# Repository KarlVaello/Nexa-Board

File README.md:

### NOTES!

In need of satisfying the ISO 15765-2 the board will receive hardware changes.

ISO 15765-2, or ISO-TP (Transport Layer), is an international standard for sending data packets over a CAN-Bus. The protocol allows for the transport of messages that exceed the eight byte maximum payload of CAN frames. ISO-TP segments longer messages into multiple frames, adding metadata that allows the interpretation of individual frames and reassembly into a complete message packet by the recipient. It can carry up to 4095 bytes of payload per message packet.

Full duplex RS-485 will be replaced by CAN-bus.

### What is Nexa-Board?
Nexa-Board is an open source project, based on STM32F103 microcontroller with a full duplex RS-485 to create a multipoint network that allows receiving and sending the information of all the boards.
RS-485 as a physical layer and by programming you can set your own data exchange and interpretation protocol.

Hardware characteristics
-	72 MHz
-	Full duplex RS-485 fully configurable.
- CAN-BUS
-	17 GPIO pins
- 7 to 15 V power input
-	Power input polarity protection

### Why does it exist ?
Exist as a solution to get a fully configurable comunication protocol, that allow you to create your own protocol depending on your needs.

### Getting Started
- Get a Nexa Board

### Project that use Nexa-Board
- Nexa Home

### TODO 
- [x] Board design (Schematic)
- [x] Board design (PCB)
- [x] PCB manufacture
- [ ] HW test
- [ ] HW final version
---------------
- [ ] New hardware changes due to apply CAN-bus
- [x] Board design (Schematic)
- [x] Board design (PCB)
- [x] PCB manufacture
- [ ] HW test
- [ ] HW final version

### Releases
 | [v1.0](https://github.com/KarlVaello/Nexa-Board/releases/tag/v1.0) - Initial complete board concept

### License
- [GPL-3.0](https://github.com/KarlVaello/Nexa-Board/blob/master/LICENSE.md)

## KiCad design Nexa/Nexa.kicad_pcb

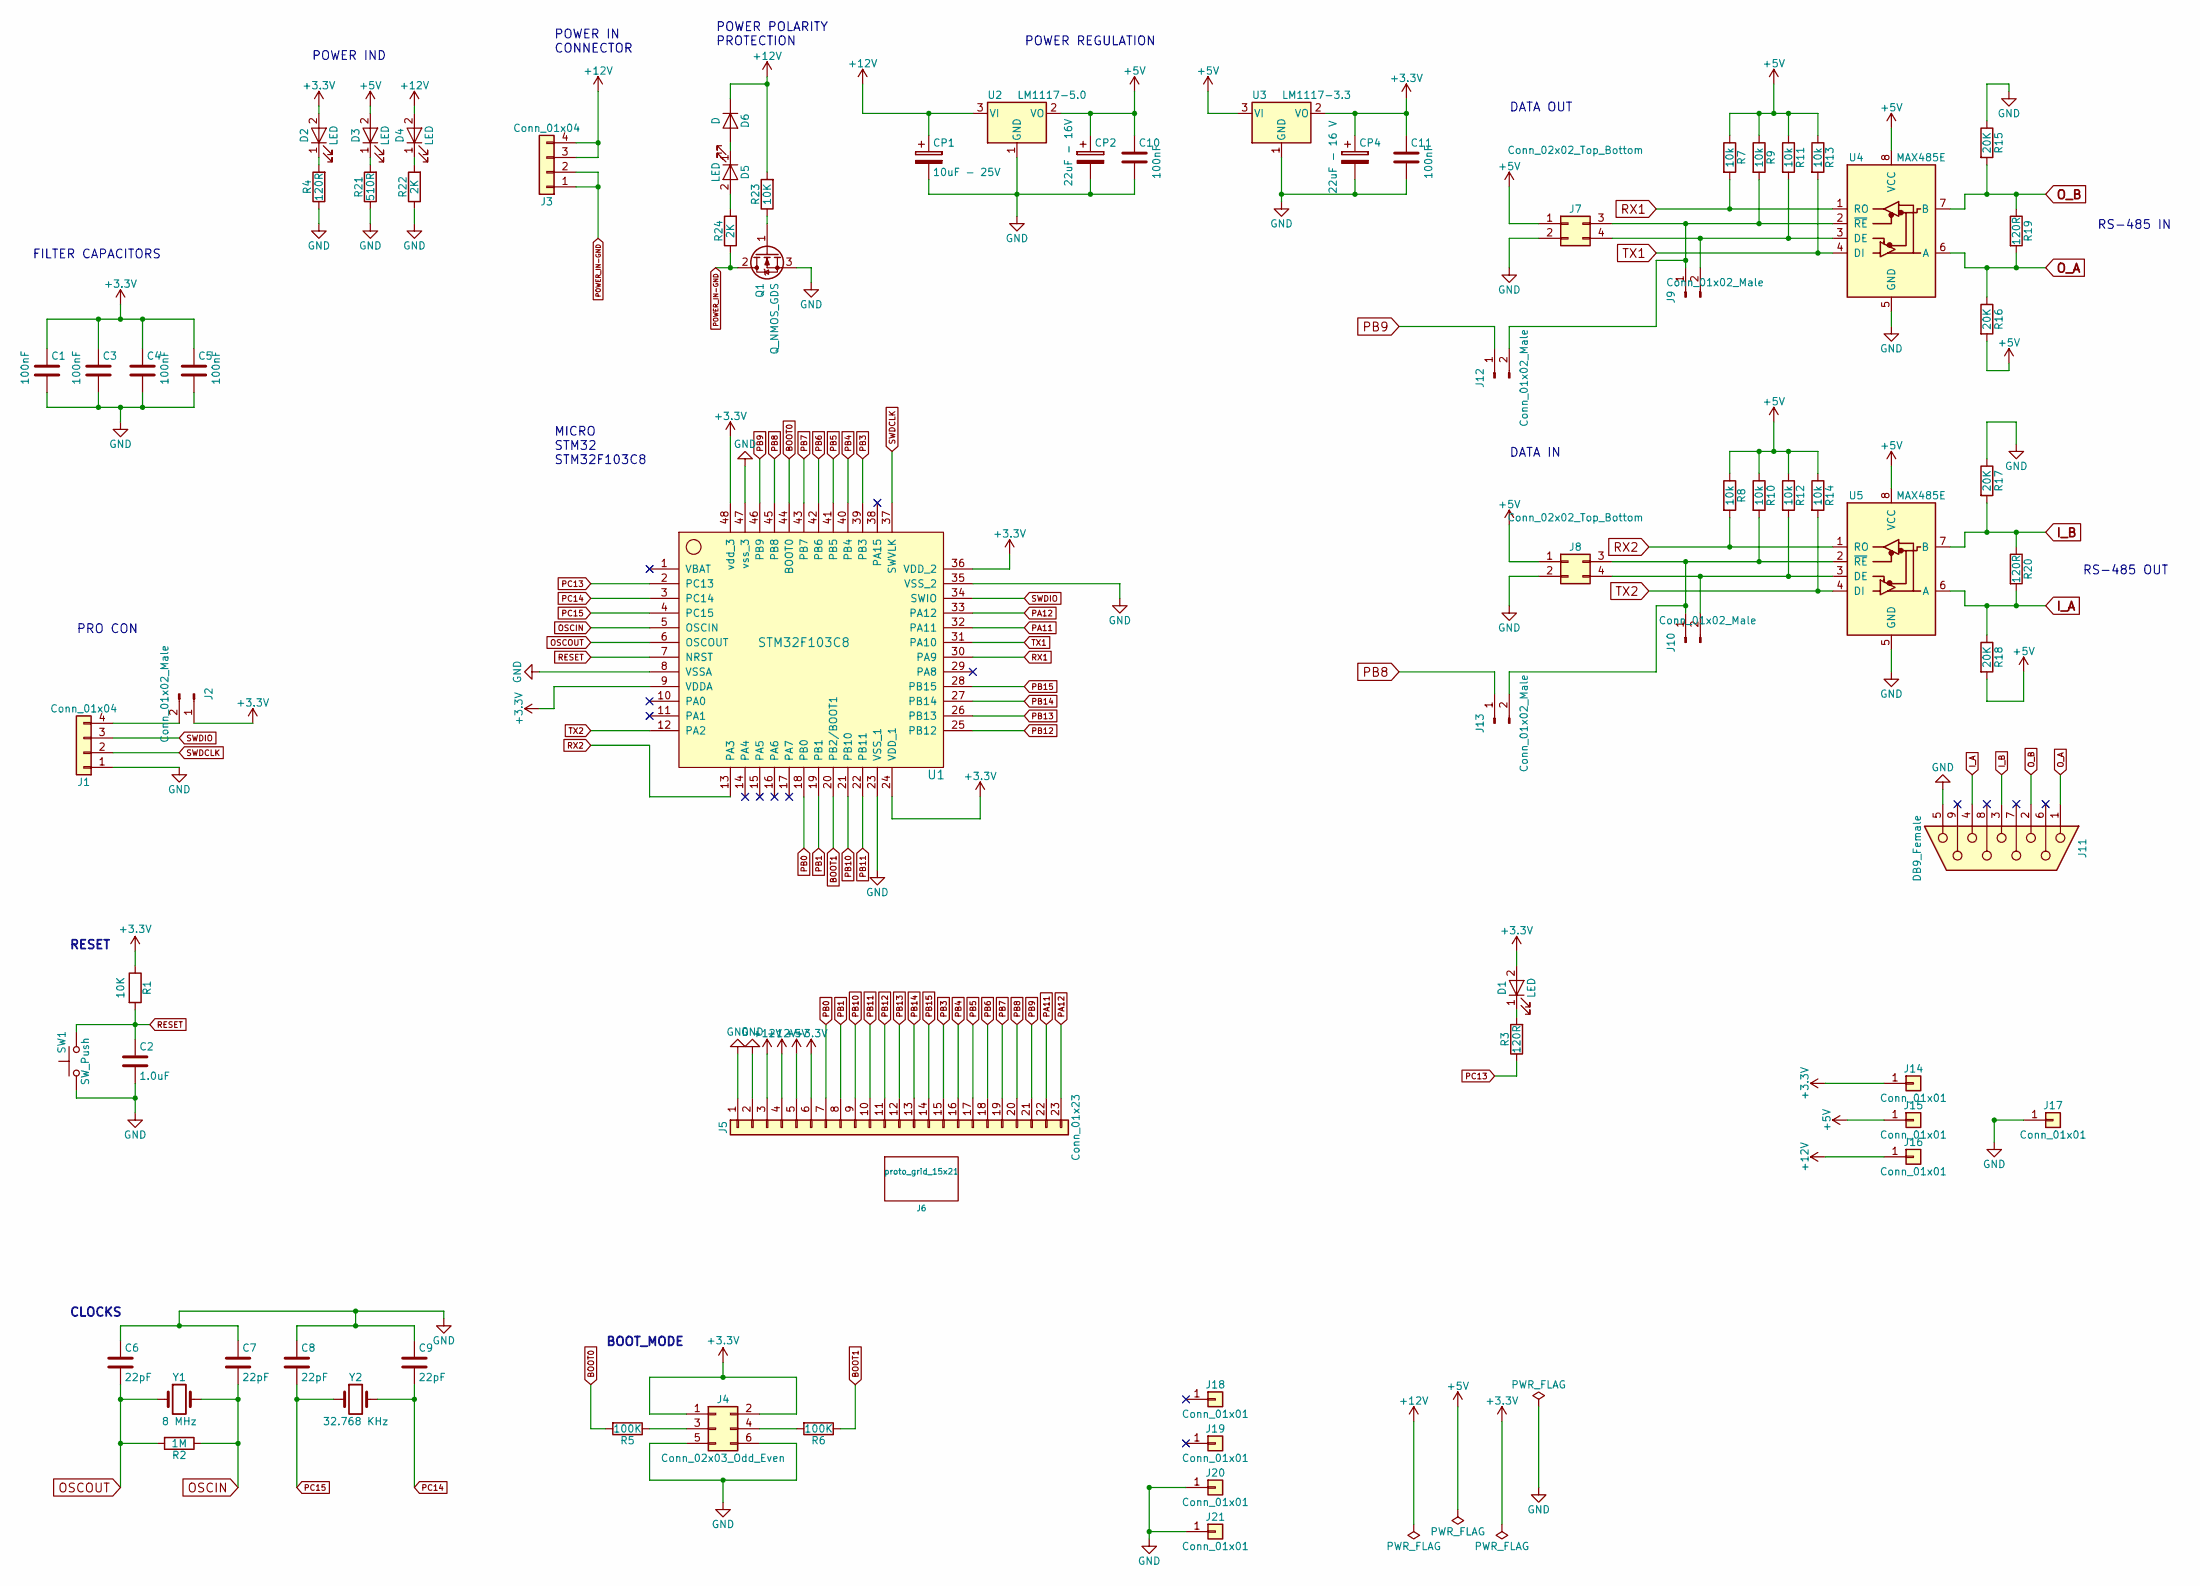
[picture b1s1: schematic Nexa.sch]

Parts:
C1, C3, C4, C5: 100nF; C_0603_HandSoldering
C2: 1.0uF; C_0603_HandSoldering
C6, C7, C8, C9: 22pF; C_0603_HandSoldering
C10, C11: 100nF; C_0805_HandSoldering
CP1: 10uF - 25V; CP_Tantalum_Case-C_EIA-6032-28_Hand
CP2: 22uF - 16V; CP_Tantalum_Case-B_EIA-3528-21_Hand
CP4: 22uF - 16 V; CP_Tantalum_Case-B_EIA-3528-21_Hand
D1, D2, D3, D4, D5: LED; LED_0805_HandSoldering
D6: D; D_SMB
J1: Conn_01x04; Pin_Header_Straight_1x04_Pitch2.54mm
J2, J9, J10, J12, J13: Conn_01x02_Male; Pin_Header_Straight_1x02_Pitch2.54mm
J3: Conn_01x04; Molex_MiniFit-JR-5569-04A2_2x02x4.20mm_Angled
J4: Conn_02x03_Odd_Even; Pin_Header_Straight_2x03_Pitch2.54mm
J5: Conn_01x23; Socket_Strip_Straight_1x23_Pitch2.54mm
J6: proto_grid_15x21; grid
J7, J8: Conn_02x02_Top_Bottom; Pin_Header_Straight_2x02_Pitch2.54mm
J11: DB9_Female
J14, J15, J16: Conn_01x01; Pin_Header_Straight_1x01_Pitch2.54mm
J17: Conn_01x01; Measurement_Point_Round-TH_Small
J18, J19, J20, J21: Conn_01x01; MountHoles_H3.2mm_D5.5
Q1: Q_NMOS_GDS; TO-252-2
R1, R23: 10K; R_0603_HandSoldering
R2: 1M; R_0603_HandSoldering
R3, R4, R19, R20: 120R; R_0603_HandSoldering
R5, R6: 100K; R_0603_HandSoldering
R7, R8, R9, R10, R11, R12, R13, R14: 10k; R_0603_HandSoldering
R15, R16, R17, R18: 20K; R_0603_HandSoldering
R21: 510R; R_0603_HandSoldering
R22, R24: 2K; R_0603_HandSoldering
SW1: SW_Push; SW_PUSH_6mm_h8.5mm
U1: STM32F103C8; LQFP-48_7x7mm_Pitch0.5mm
U2: LM1117-5.0; SOT-223
U3: LM1117-3.3; SOT-223
U4, U5: MAX485E; SOIC-8_3.9x4.9mm_Pitch1.27mm
Y1: 8 MHz; Crystal_HC49-4H_Vertical
Y2: 32.768 KHz; Crystal_SMD_SeikoEpson_MC306-4pin_8.0x3.2mm_HandSoldering

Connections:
+3V3: C1.1, C3.1, C4.1, C5.1, C11.1, CP4.1, D1.2 (A), D2.2 (A), J2.1, J4.1, J4.2, J5.6, J14.1, R1.1, U1.9 (VDDA), U1.24 (VDD_1), U1.36 (VDD_2), U1.48 (vdd_3), U3.2 (VO)
+5V: C10.1, CP2.1, D3.2 (A), J5.5, J7.1, J8.1, J15.1, R7.1, R8.1, R9.1, R10.1, R11.1, R12.1, R13.1, R14.1, R16.2, R18.2, U2.2 (VO), U3.3 (VI), U4.8 (VCC), U5.8 (VCC)
+12V: CP1.1, D4.2 (A), D6.1 (K), J3.3, J3.4, J5.3, J5.4, J16.1, R23.2, U2.3 (VI)
BOOT0: R5.2, U1.44 (BOOT0)
BOOT1: R6.1, U1.20 (PB2/BOOT1)
GND: C1.2, C2.2, C3.2, C4.2, C5.2, C6.1, C7.1, C8.1, C9.1, C10.2, C11.2, CP1.2, CP2.2, CP4.2, J1.1, J4.5, J4.6, J5.1, J5.2, J7.2, J8.2, J11.5, J17.1, J20.1, J21.1, Q1.3 (S), R4.1, R15.1, R17.1, R21.1, R22.1, SW1.1, U1.8 (VSSA), U1.23 (VSS_1), U1.35 (VSS_2), U1.47 (vss_3), U2.1 (GND), U3.1 (GND), U4.5 (GND), U5.5 (GND)
I_A: J11.4, R18.1, R20.2, U5.6 (A)
I_B: J11.3, R17.2, R20.1, U5.7 (B)
unnamed: D1.1 (K), R3.2
unnamed: D2.1 (K), R4.2
unnamed: D3.1 (K), R21.2
unnamed: D4.1 (K), R22.2
unnamed: D5.1 (K), D6.2 (A)
unnamed: D5.2 (A), R24.2
unnamed: J1.4, J2.2
unnamed: J4.3, R5.1
unnamed: J4.4, R6.2
unnamed: J7.4, J9.2, R11.2, U4.3 (DE)
unnamed: J8.3, J10.1, J13.2, R10.2, U5.2 (~RE)
unnamed: J8.4, J10.2, R12.2, U5.3 (DE)
unnamed: J7.3, J9.1, J12.2, R9.2, U4.2 (~RE)
unnamed: Q1.1 (G), R23.1
OSCIN: C7.2, R2.1, U1.5 (OSCIN), Y1.2
OSCOUT: C6.2, R2.2, U1.6 (OSCOUT), Y1.1
O_A: J11.1, R16.1, R19.2, U4.6 (A)
O_B: J11.2, R15.2, R19.1, U4.7 (B)
PA11: J5.22, U1.32 (PA11)
PA12: J5.23, U1.33 (PA12)
PB0: J5.7, U1.18 (PB0)
PB1: J5.8, U1.19 (PB1)
PB3: J5.15, U1.39 (PB3)
PB4: J5.16, U1.40 (PB4)
PB5: J5.17, U1.41 (PB5)
PB6: J5.18, U1.42 (PB6)
PB7: J5.19, U1.43 (PB7)
PB8: J5.20, J13.1, U1.45 (PB8~)
PB9: J5.21, J12.1, U1.46 (PB9)
PB10: J5.9, U1.21 (PB10)
PB11: J5.10, U1.22 (PB11)
PB12: J5.11, U1.25 (PB12)
PB13: J5.12, U1.26 (PB13)
PB14: J5.13, U1.27 (PB14)
PB15: J5.14, U1.28 (PB15)
PC13: R3.1, U1.2 (PC13)
PC14: C9.2, U1.3 (PC14), Y2.2
PC15: C8.2, U1.4 (PC15), Y2.1
POWER_IN-GND: J3.1, J3.2, Q1.2 (D), R24.1
RESET: C2.1, R1.2, SW1.2, U1.7 (NRST)
RX1: R7.2, U1.30 (PA9), U4.1 (RO)
RX2: R8.2, U1.13 (PA3), U5.1 (RO)
SWDCLK: J1.2, U1.37 (SWVLK)
SWDIO: J1.3, U1.34 (SWIO)
TX1: R13.2, U1.31 (PA10), U4.4 (DI)
TX2: R14.2, U1.12 (PA2), U5.4 (DI)

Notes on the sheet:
DATA OUT
DATA IN
RESET
CLOCKS
BOOT_MODE
FILTER CAPACITORS
POWER REGULATION
RS-485 IN
RS-485 OUT
POWER IND
POWER POLARITY PROTECTION
POWER IN CONNECTOR
PRO CON
MICRO STM32 STM32F103C8

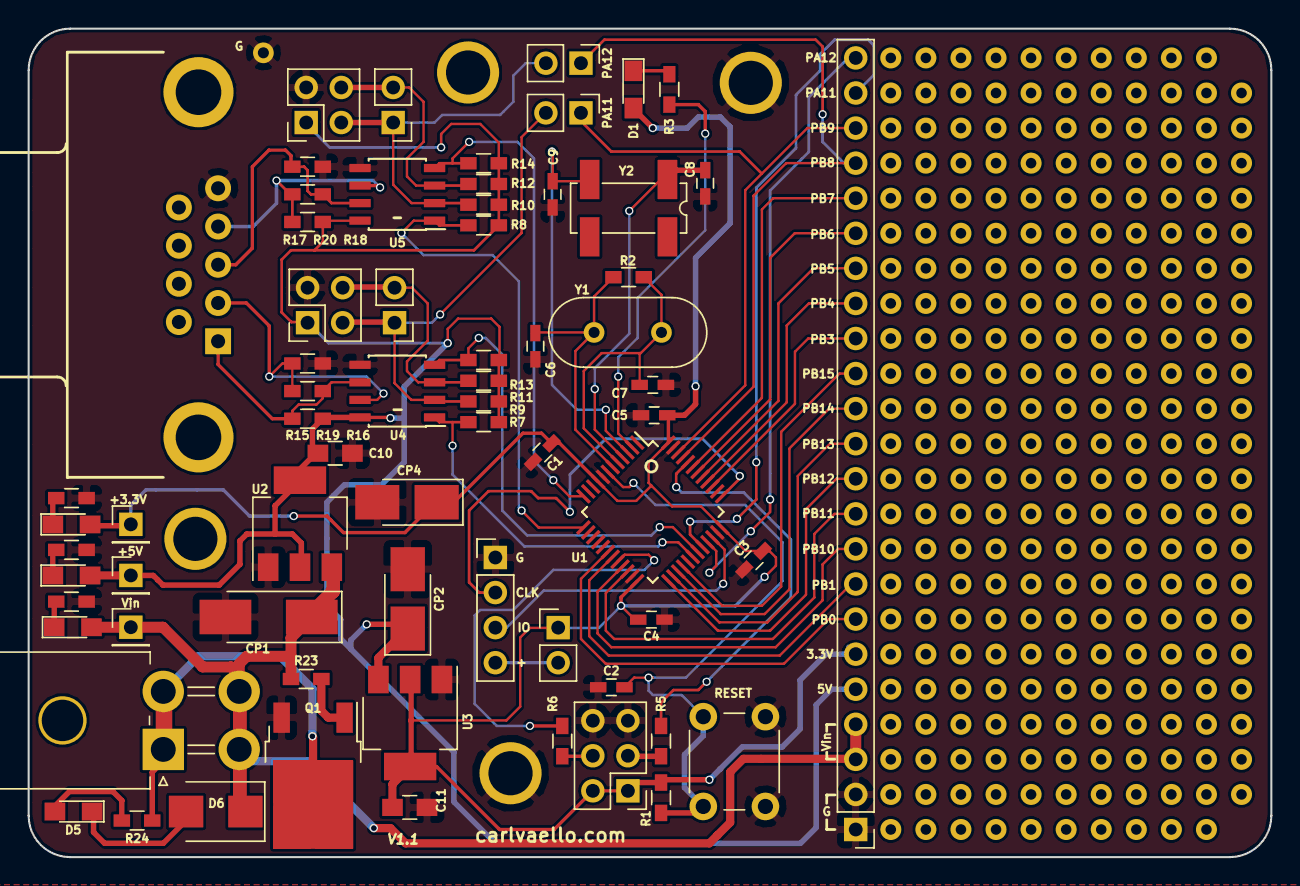
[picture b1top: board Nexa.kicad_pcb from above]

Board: 2 copper layers, 90.0 x 60.0 mm, 74 parts (0 on the bottom side), 54 nets.

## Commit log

2018-01-11 :octocat: Added .gitattributes & .gitignore files
2018-01-11 Board Hardware files
    Hardware files on KiCad v1.0
2018-01-11 ignore file update
2018-01-11 license
2018-01-19 Issue #1 and #2 closed
    #1 Polarity protection N_Mosfet is NOT correct configured
    Mosfets had incorrect pinout.
    #2 CP1 (10nF-16V), max V should be oversize
    CP1 is now a 25V cap
2018-01-19 Nexa logo
2018-02-13 CHANGES - CAN BUS
